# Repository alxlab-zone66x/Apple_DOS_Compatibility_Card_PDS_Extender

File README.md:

# PDS DOS Compatibility Card Extender

This repo includes the original PDS DOS Compatibility Card Extender made by tomytronics on reddit called Replacement Extender Card for Apple DOS Compatibility v 1.0.

It was inspired by the original Reply  Extender Card.

This allows you to use the Houdini I and Houdini II PDS DOS Compatibility cards in computers like the Macintosh Quadra 700 and Macintosh Quadra 950.

### Notes from tomytronics for his design

"My original design fits perfectly but is prone to interference without wrapping them in foil and connecting them to ground screws."

"You are free to upload the original and modified files anywhere. The only important part to know is to keep the board’s width, the location of the connector on the DOS card side, and the 4 holes unchanged. The  connector on the other side should be the same to use the same bracket  off the Reply DOS cards or you could change it to break out game port  and VGA port rather than to rely on hard to find cable."

### Future Plans

I will be modifying tomytronics' original design to fix the interference issues. I will also add a 3.5mm headphone jack. There will probably be two or 3 versions of the extender. One will have the original HD-26 connect

## Bill of Materials

| Quantity | Product Number   | Datasheet                         |
| :------- | ---------------- | --------------------------------- |
| 1        | L717HDA26PD1CH4F | [pdf](/docs/L717HDA26PD1CH4F.pdf) |
| 1        | L77HDA26SD1CH4F  | [pdf](/docs/L77HDA26SD1CH4F.pdf)  |

## License

This work is licensed under a <a rel="license" href="http://creativecommons.org/licenses/by-nc-sa/4.0/">Creative Commons Attribution-NonCommercial-ShareAlike 4.0 International License</a>.

## Community

For more great retro hardware projects and a great community check out:

Join us in #skunkworks on [Discord](https://discord.gg/GKcvtgU7P9) to help make retro solutions available to all.

## Special Thanks

tomytronics, [warmech](https://tinkerdifferent.com/members/warmech.174/), [Ron's Computer Videos](https://tinkerdifferent.com/members/rons-computer-videos.38/)

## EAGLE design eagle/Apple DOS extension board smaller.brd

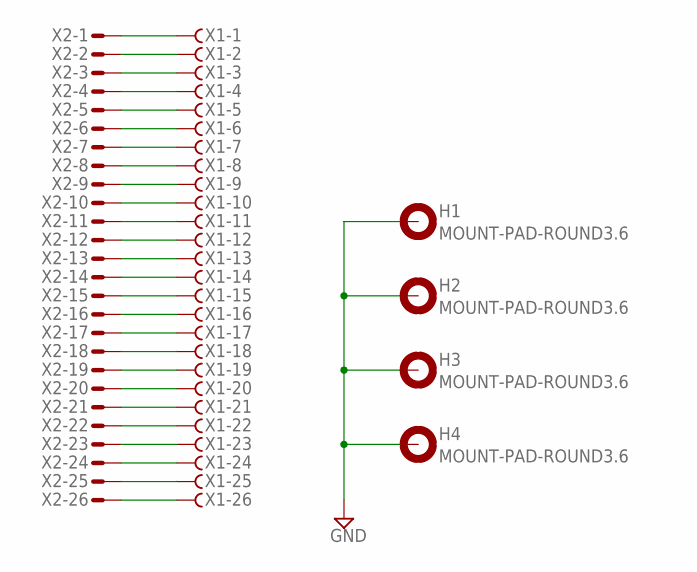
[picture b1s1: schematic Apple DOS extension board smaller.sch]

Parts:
H1, H2, H3, H4: MOUNT-PAD-ROUND3.6; 3,6-PAD
X1: HF26HS; HDF26H
X2: HM26HS; HDM26H

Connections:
GND: H1.B3,6, H2.B3,6, H3.B3,6, H4.B3,6
unnamed: X1.1, X2.1
unnamed: X1.2, X2.2
unnamed: X1.3, X2.3
unnamed: X1.4, X2.4
unnamed: X1.5, X2.5
unnamed: X1.6, X2.6
unnamed: X1.7, X2.7
unnamed: X1.8, X2.8
unnamed: X1.9, X2.9
unnamed: X1.10, X2.10
unnamed: X1.11, X2.11
unnamed: X1.12, X2.12
unnamed: X1.13, X2.13
unnamed: X1.14, X2.14
unnamed: X1.15, X2.15
unnamed: X1.16, X2.16
unnamed: X1.17, X2.17
unnamed: X1.18, X2.18
unnamed: X1.19, X2.19
unnamed: X1.20, X2.20
unnamed: X1.21, X2.21
unnamed: X1.22, X2.22
unnamed: X1.23, X2.23
unnamed: X1.24, X2.24
unnamed: X1.25, X2.25
unnamed: X1.26, X2.26

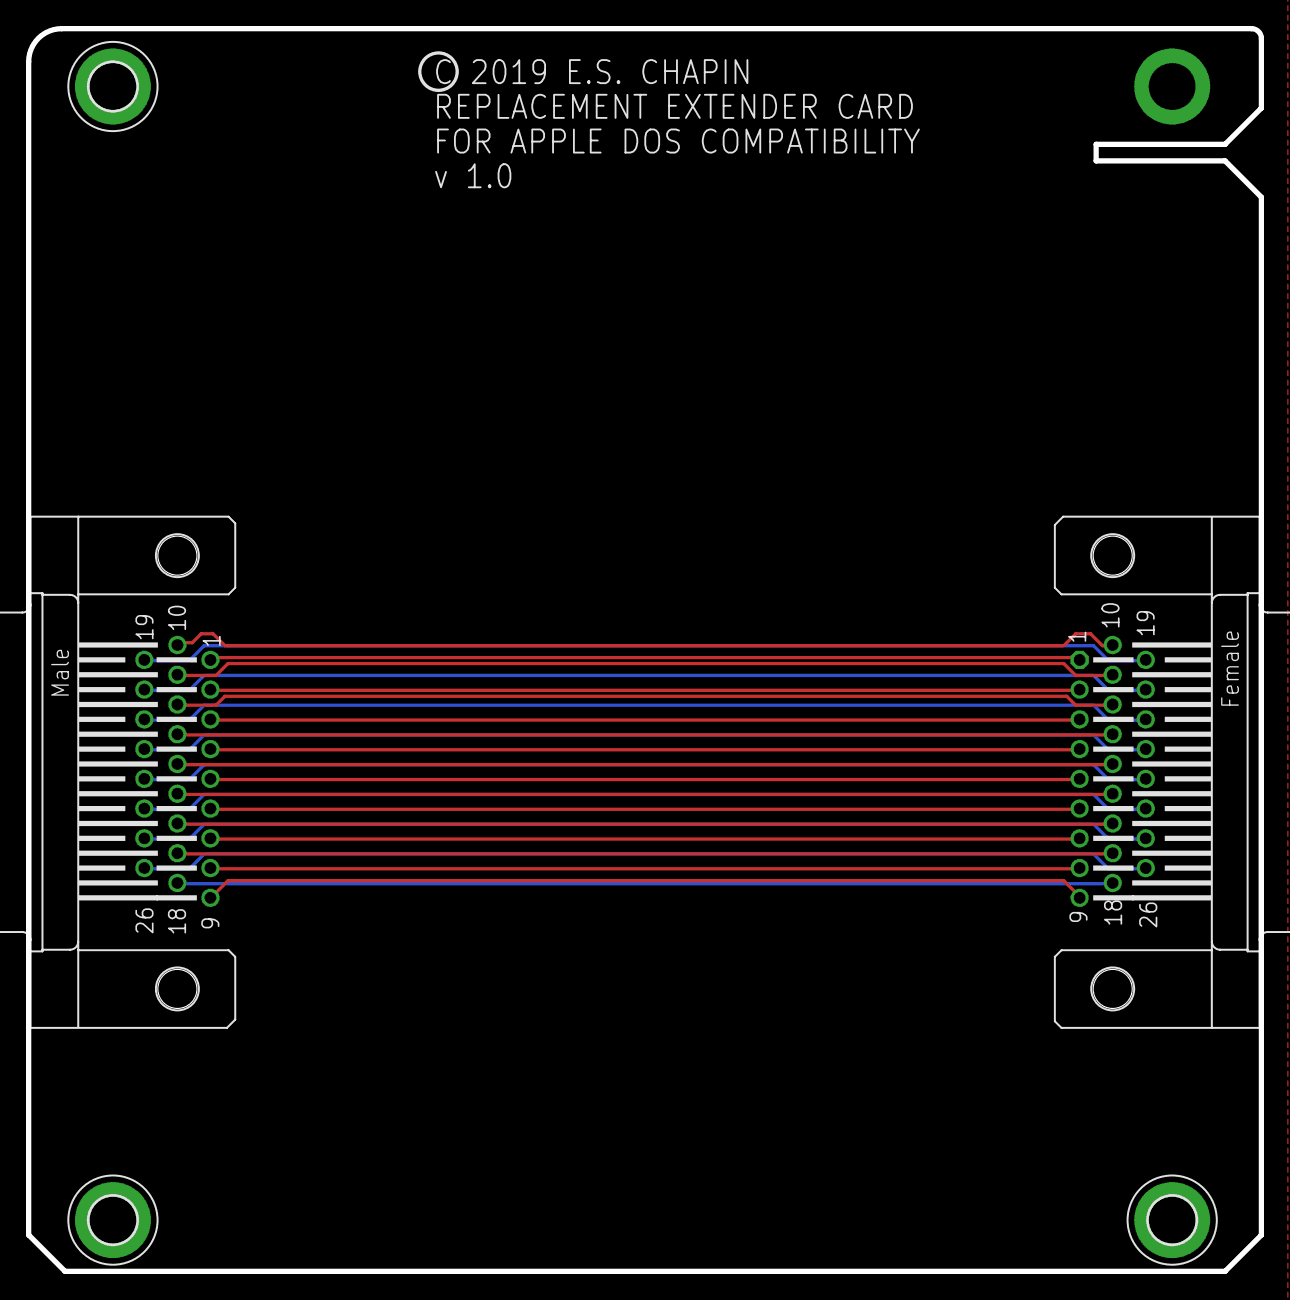
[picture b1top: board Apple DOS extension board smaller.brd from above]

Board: 2 copper layers, 94.7 x 95.5 mm, 6 parts (1 on the bottom side), 27 nets.
